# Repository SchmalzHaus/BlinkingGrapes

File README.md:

# BlinkingGrapes
A learn to solder circuit board . Also, my first board I designed.

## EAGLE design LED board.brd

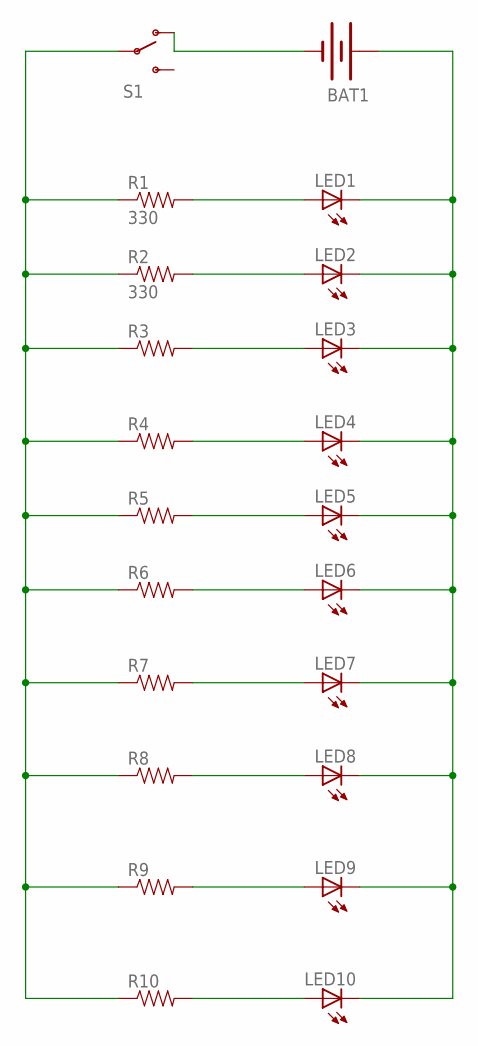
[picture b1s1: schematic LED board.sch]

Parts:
BAT1: BATTERY20PTH; BATTCOM_20MM_PTH
LED1, LED2, LED3, LED4, LED5, LED6, LED7, LED8, LED9, LED10: LED5MM
R1, R2: 330; AXIAL-0.4
R3, R4, R5, R6, R7, R8, R9, R10: RESISTORPTH-1/4W; AXIAL-0.4
S1: SWITCH-SPDTPTH; SWITCH-SPDT

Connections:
unnamed: BAT1.2 (-), S1.1 (O)
unnamed: R1.P$1 (1), R2.P$1 (1), R3.P$1 (1), R4.P$1 (1), R5.P$1 (1), R6.P$1 (1), R7.P$1 (1), R8.P$1 (1), R9.P$1 (1), R10.P$1 (1), S1.2
unnamed: LED1.A, R1.P$2 (2)
unnamed: LED2.A, R2.P$2 (2)
unnamed: LED3.A, R3.P$2 (2)
unnamed: LED4.A, R4.P$2 (2)
unnamed: LED5.A, R5.P$2 (2)
unnamed: BAT1.1 (+), LED1.K (C), LED2.K (C), LED3.K (C), LED4.K (C), LED5.K (C), LED6.K (C), LED7.K (C), LED8.K (C), LED9.K (C), LED10.K (C)
unnamed: LED6.A, R6.P$2 (2)
unnamed: LED7.A, R7.P$2 (2)
unnamed: LED8.A, R8.P$2 (2)
unnamed: LED9.A, R9.P$2 (2)
unnamed: LED10.A, R10.P$2 (2)

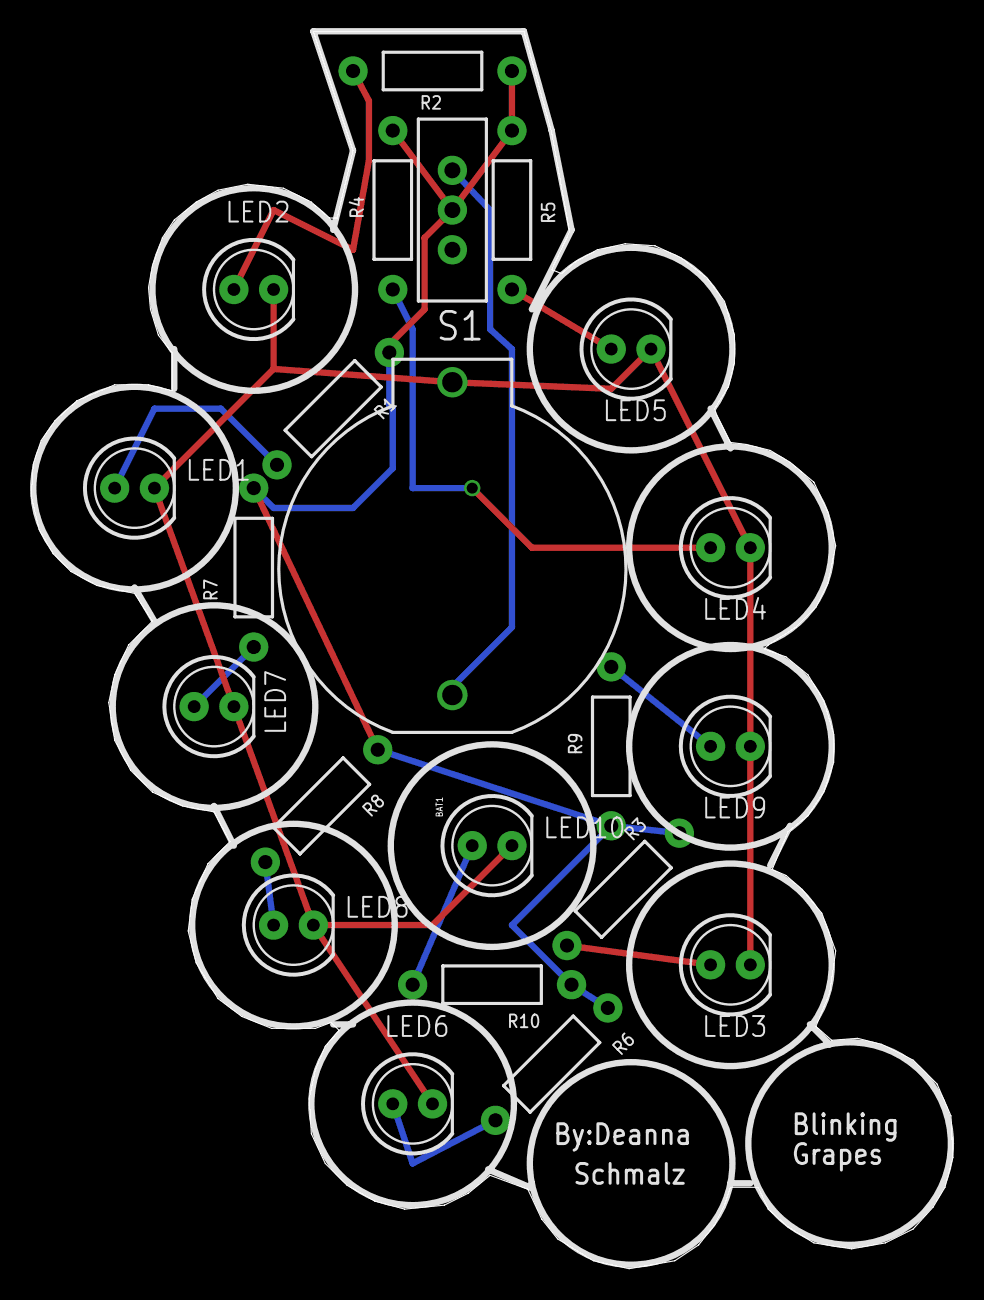
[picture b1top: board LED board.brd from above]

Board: 2 copper layers, 58.9 x 79.1 mm, 22 parts (0 on the bottom side), 13 nets.

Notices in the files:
parts and their libraries:
SparkFun-Electromechanical: Licensing: Creative Commons ShareAlike 4.0 International - https://creativecommons.org/licenses/by-sa/4.0
